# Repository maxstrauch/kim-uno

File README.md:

# KIM Uno

_A portable, software defined dev kit for (retro) microprocessors_

Back in late 2018 it came to my mind, that I wanted to build a small portable microprocessor dev kit, just like the famous [KIM-1](https://en.wikipedia.org/wiki/KIM-1) from MOS Technology, Inc. and designed by Chuck Peddle who was also involved in creating the 6502 CPU.

Therefore, I designed the KIM Uno as a portable device, which fits in one hand and is powered by two CR2032 batteries. It uses the ATMega328p ("Arduino") microcontroller running at 8 MHz to emulate (or simulate) a desired CPU. This architecture also makes sure, that the emulated CPUs are interchangeable to anything which fits inside the microcontroller's flash memory. So it is a multi-purpose device.

Currently this project emulates an [OISC](https://en.wikipedia.org/wiki/One_instruction_set_computer) with just one instruction `subleq`. The idea came to me when I watched [The Ultimate Apollo Guidance Computer Talk](https://www.youtube.com/watch?v=xx7Lfh5SKUQ) and then discovered [this GitHub repo](https://github.com/davidar/subleq).

There is another pretty interesting project, called the same (KIM Uno), which does a real replica of the 6502 KIM Uno. Check it out [here](https://obsolescence.wixsite.com/obsolescence/kim-uno-summary-c1uuh). The creator even sells the kit. So if you are interested in 6502 and like this project, you should take a look there!

# Links

You can find:

 - a very detailed series of build instructions on Instructable: https://www.instructables.com/id/The-KIM-Uno-a-5-Microprocessor-Dev-Kit-Emulator/
 - a video demonstrating the device on YouTube: https://youtu.be/oWd1w513VB8

# Contents of this repository

This repository contains all needed documents, to create your own KIM Uno. In the root of the repository you can find the following important documents:

 - `bom_kim-uno-rev1.ods` - A bill of materials and rough calculation of the material cost (it's about 4,75 € as of 2018) and links to the components on Ebay. The offers on Ebay might be closed (depends on when you read this here) but this might be a good starting point for sourcing the components.
 - `kim-uno-rev1_2018-12-12_gerbers.zip` - A zip file containing the latest Gerber and drill files for production. I send exactly those files out to PCBWay to produce the PCBs. The files are exported to the specifications of PCBWay (see https://www.pcbway.com/blog/help_center/Generate_Gerber_file_from_Kicad.html) but might work also for another manufacturer.
 - `kim-uno-rev1-schematic.pdf` - The schematic of the project. [Show schematics.](https://raw.github.com/maxstrauch/kim-uno/master/kim-uno-rev1-schematic.pdf)
 - `arduino-isp.ino` - An Arduino sketch of the ISP code I use on my Arduino UNO to program the microcontrollers

This are the essential three documents you'll need to reproduce my KIM Uno. Furthermore, the following directories can be found in the repository:

 - `images` - Just images of the project
 - `kicad` - The original KiCad files, so that you can make modifications as you like (see also the License section at the end)
 - `src` - The source code for the microcontroller firmware; you can either use `src/main.hex` and burn it onto your ATMega328p or you can modify `src/main.c`, recompile it (see `src/Makefile`) and then burn it with your own changes
 - `tools` - A little NodeJS based assembler and simulator of the KIM Uno

# Flashing the firmware

In the directory `src/` you can find the source code for the emulator along with an already compiled `src/main.hex` which you can directly upload to the microcontroller.

Before you can actually use it, you need to set the fuse bits of the microcontroller, so that it uses the internal 8 MHz clock without dividing it in half. You can get the job done with the following command:

    avrdude -c stk500v1 -b 9600 -v -v -P /dev/cu.usbmodem1421 -p m328p -U lfuse:w:0xe2:m -U hfuse:w:0xd9:m -U efuse:w:0xff:m

After this you can flash the firmware onto the microcontroller with this command:

    avrdude -c stk500v1 -b 9600 -v -v -P /dev/cu.usbmodem1421 -p m328p -U flash:w:main.hex

Maybe you need to change the argument for `-P`.

You can also use the `src/Makefile` to do this tasks. Run `make all` to compile (GNU AVR toolchain required to be installed) and `make install` to flash it. You can use `make fuse` to set the fuses correctly.

# Theory of operation

## Basics

The KIM Uno does emulate a One Instruction Set Computer (OISC) and provides the subleq instruction to perform computation.

The subleq instruction stands for subtract and branch if less than or equal to zero. In pseudo-code this looks like the following:

    subleq A B C: mem[B] = mem [B] - mem[A]; 
                  if (mem[B] <= 0) goto C;

Since the KIM Uno emulates a 8-bit machine, all arguments A, B and C are 8 bit values and therefore it can address a total main memory of 256 byte. Obviously this can be extended, by making A, B and C multi-byte values. But for now let's keep it simple.

The KIM Uno has also "peripherals": the display and keyboard. It uses a memory mapped architecture to interface those peripherals, although the memory map is very simple:

 - 0x00 = the Z register (zero) and should be kept zero.
 - 0x01 - 0x06 = six bytes which represent the value of every of the display segments (from right to left). A value <= 0xf (16) can be placed in one of this memory locations and it will appear on the seven segment display. There are some special characters to show which can be displayed setting a value > 0xf - see the source code (main.c) for more details.
 - 0x07, 0x08, 0x09 = three bytes where every byte represents two seven segment displays (from right to left). This memory locations allow simply displaying a result without splitting up the result into two nibbles to place it in the single digit memory locations 0x01 - 0x06.
 - 0x0a+ = A program starts at 0x0a. Currently the "Go" key executes from 0x0a fixed.

## Pseudo instructions

There are three "pseudo instructions" which make life easier when programming for the KIM Uno. They are composed of multiple `subleq` instructions:

**MOV a, b - copy data at location a to b can be composed of:**

    subleq b, b, 2 (next instruction)
    subleq a, Z, 3 (next instruction)
    subleq Z, b, 4 (next instruction)
    subleq Z, Z, e.g. 5 (next instruction)

Using the subtraction feature of `subleq`, which `does mem[b] - mem[a]` and overwrites `mem[b]` with the result, the value is copied using the zero register. And `subleq Z, Z, ...` simply resets the zero register to 0, regardless of the value of Z.

**ADD a, b - adds the values a + b and stores the sum in b can be composed of:**

    subleq a, Z, 2 (next instruction)
    subleq Z, b, 3 (next instruction)
    subleq Z, Z, e.g. 4 (next instruction)

This instruction simply calculates `mem[b] - (- mem[a])` which is `mem[b] + mem[a]` by also using the subtraction feature.

**HLT - halts the CPU and ends the execution:**

By definition the emulator knows that the CPU wants to terminate if it jumps to 0xff (or -1 if singed). So a simple

    subleq Z, Z, -1

does the job and indicates to the emulator, that it should end emulation.

## Fibonacci example program

With this information one can now write a program in assembler, for example Fibonacci's algorithm:

    .def n   0xfa 6             ; Input n for fibonacci
    .def a   0xfc 0
    .def b   0xfd 1
    .def out 0x07 0             ; Output register for display

    ; Temp registeres, needed since the subleq instructions modify the original
    ; registers (the program might be optimized to use only one tmp register)
    .def tmp1 0xfe 0
    .def tmp2 0xff 0

    ; Constant values. Since subleq has no immediate instructions we store
    ; those values in a register
    .def Z   0x00 0
    .def one 0xfb 1
    .def two 0xf9 2

        mov n, tmp1             ; Copy n to tmp1 to perform calculation on it
        subleq two, tmp1, done  ; If n <= 2, we're done and goto the end
        subleq one, n, loop     ; Start computation with n := n-1

    loop:
        mov a, tmp1             ; Save a and ...
        mov b, tmp2             ; ... b to perform the addition on it
        add tmp1, tmp2          ; Save the sum of a and b on tmp2
        mov b, a                ; Set a to the value of b
        mov tmp2, b             ; Set b to tmp2 which is a + b
        subleq one, n, done     ; Decrement n
        subleq Z, Z, loop       ; Check if n > 0 and continue computation

    done:
        mov b, out              ; Finished ;-) - output the value on b
        hlt                     ; Halt the CPU

This is basically the content of `tools/fibonacci/fibonacci.s`. This program can now be turned into `subleq` CPU instructions and entered into the memory of the KIM Uno and then executed. Since there is only one instruction, only the arguments (A, B and C) are entered. So after three memory locations the next instruction arguments begin and so forth.

But there is a faster way, shown in the next section.

## Further tools

The `tools/` directory contains some basic assembler and simulator for the KIM Uno. They are written in [NodeJS](https://nodejs.org/en/) - make sure that you have installed it.

**Assembling programs**

If you take a look at "tools/fibonacci/fibonacci.s" you'll find that it is the source code for the discussed fibonacci implementation. To assemble it and make a program out of it, that the KIM Uno can run, you enter the following command (in `tools/`):

    node assemble.js fibonacci/fibonacci.s

and it will either print an error if you made a mistake or spill out the resulting program. To save it, you can copy the output and save it to a file or simply run this command:

    node assemble.js fibonacci/fibonacci.s > yourfile.h

The output is formatted in a way that it can be directly included in the KIM Uno firmware as a C header file, but the simulator can also use it to simulate. Simply enter:

    node sim.js yourfile.h

And you will be presented with the simulation result and the output expected from the KIM Uno on the display.

# Conclusion

## Design flaws in the PCB design

After completing this project I found a couple of points which are noteworthy and should be addressed in a new revision of the PCB board:

- the ATMega328p's silk screen has not the usual notch where the first pin is located. The DIP-28 footprint does not even have a square pad where the first pin is located. This should definitely be improved with a more detailed silkscreen to prevent confusion
- the ISP header has no connection labels on the silk screen. This makes it difficult to recognize how to connect it to the ISP
- the ISP header could be changed into a 2x6 pin header with a standard pin layout to prevent any confusion

Apart from those points I'm pretty happy how it turned out and worked on the first try.

## Further uses

But the journey does not end here - there are an infinite number of options how you could modify the KIM Uno and customize it to your needs and liking.

For example the KIM Uno could be equipped with a "real" retro CPU emulator which might emulate the famous MOS 6502 or Intel 8085, 8086 or 8088. Then it would go the way to my initial vision, before I learned about OISCs.

But there are possible other uses, since the hardware design is pretty generic. The KIM Uno could be used as:

- a remote controller e.g. for CNCs or other devices. Maybe wired or equipped with an IR diode or any other wireless sender
- a (hexadecimal) pocket calculator. The firmware can be adapted very easily and the board design does not need to be changed very much. Maybe the silkscreen can be adapted with math operations and the gap between the segments can be removed. Apart from this, it is already ready for this transformation

_**Have fun with it. Cheers!**_

# License

Creative Commons Attribution-ShareAlike 4.0 International (CC BY-SA 4.0). Click [here](http://creativecommons.org/licenses/by-sa/4.0/) for details. The license applies to the entire source code.

`This program is distributed WITHOUT ANY WARRANTY; without even the implied warranty of MERCHANTABILITY or FITNESS FOR A PARTICULAR PURPOSE.`

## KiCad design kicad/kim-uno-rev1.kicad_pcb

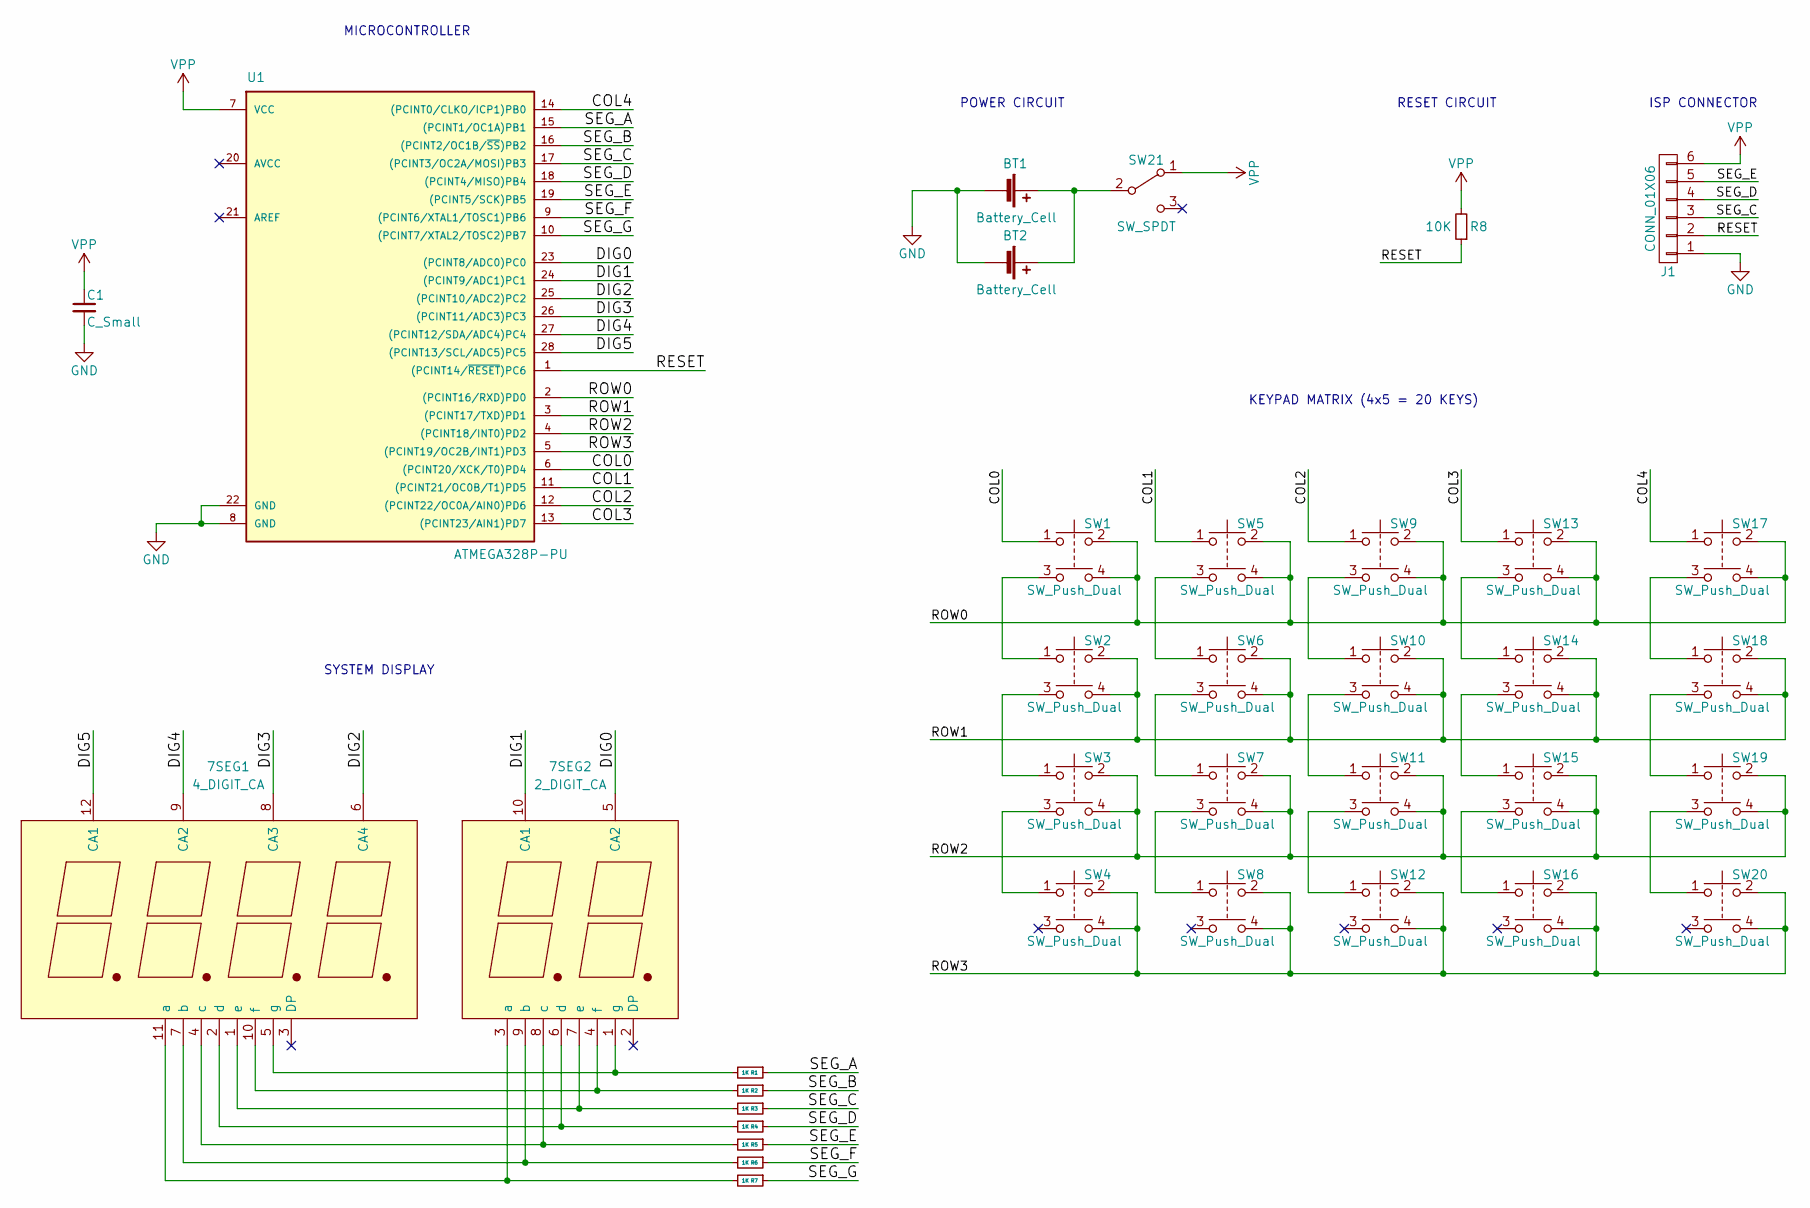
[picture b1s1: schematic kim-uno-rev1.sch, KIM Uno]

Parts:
7SEG1: 4_DIGIT_CA; 7_Segment_4_Digit
7SEG2: 2_DIGIT_CA; 7_Segment_2_Digit
BT1, BT2: Battery_Cell; CR2032SMD
C1: C_Small; C_Disc_D5.0mm_W2.5mm_P2.50mm
J1: CONN_01X06; Pin_Header_Straight_1x06_Pitch2.54mm
R1, R2, R3, R4, R5, R6, R7: 1K; R_Axial_DIN0204_L3.6mm_D1.6mm_P7.62mm_Horizontal
R8: 10K; R_Axial_DIN0204_L3.6mm_D1.6mm_P7.62mm_Horizontal
SW1, SW2, SW3, SW4, SW5, SW6, SW7, SW8, SW9, SW10, SW11, SW12, SW13, SW14, SW15, SW16, SW17, SW18, SW19, SW20: SW_Push_Dual; SMD_Tact_Switch_6x6x6_Big_Pads
SW21: SW_SPDT; Switch_SPDT_3mm
U1: ATMEGA328P-PU; DIP-28_W7.62mm

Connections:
/COL0: SW1.1, U1.6 ((PCINT20/XCK/T0)PD4)
/COL1: SW5.1, U1.11 ((PCINT21/OC0B/T1)PD5)
/COL2: SW9.1, U1.12 ((PCINT22/OC0A/AIN0)PD6)
/COL3: SW13.1, U1.13 ((PCINT23/AIN1)PD7)
/COL4: SW17.1, U1.14 ((PCINT0/CLKO/ICP1)PB0)
/DIG0: 7SEG2.5 (CA2), U1.23 ((PCINT8/ADC0)PC0)
/DIG1: 7SEG2.10 (CA1), U1.24 ((PCINT9/ADC1)PC1)
/DIG2: 7SEG1.6 (CA4), U1.25 ((PCINT10/ADC2)PC2)
/DIG3: 7SEG1.8 (CA3), U1.26 ((PCINT11/ADC3)PC3)
/DIG4: 7SEG1.9 (CA2), U1.27 ((PCINT12/SDA/ADC4)PC4)
/DIG5: 7SEG1.12 (CA1), U1.28 ((PCINT13/SCL/ADC5)PC5)
/RESET: J1.2, R8.1, U1.1 ((PCINT14/~RESET~)PC6)
/ROW0: SW1.2, SW1.4, SW5.2, SW5.4, SW9.2, SW9.4, SW13.2, SW13.4, SW17.2, SW17.4, U1.2 ((PCINT16/RXD)PD0)
/ROW1: SW2.2, SW2.4, SW6.2, SW6.4, SW10.2, SW10.4, SW14.2, SW14.4, SW18.2, SW18.4, U1.3 ((PCINT17/TXD)PD1)
/ROW2: SW3.2, SW3.4, SW7.2, SW7.4, SW11.2, SW11.4, SW15.2, SW15.4, SW19.2, SW19.4, U1.4 ((PCINT18/INT0)PD2)
/ROW3: SW4.2, SW4.4, SW8.2, SW8.4, SW12.2, SW12.4, SW16.2, SW16.4, SW20.2, SW20.4, U1.5 ((PCINT19/OC2B/INT1)PD3)
/SEG_A: R1.1, U1.15 ((PCINT1/OC1A)PB1)
/SEG_B: R2.1, U1.16 ((PCINT2/OC1B/~SS~)PB2)
/SEG_C: J1.3, R3.1, U1.17 ((PCINT3/OC2A/MOSI)PB3)
/SEG_D: J1.4, R4.1, U1.18 ((PCINT4/MISO)PB4)
/SEG_E: J1.5, R5.1, U1.19 ((PCINT5/SCK)PB5)
/SEG_F: R6.1, U1.9 ((PCINT6/XTAL1/TOSC1)PB6)
/SEG_G: R7.1, U1.10 ((PCINT7/XTAL2/TOSC2)PB7)
GND: BT1.2 (-), BT2.2 (-), C1.2, J1.1, U1.8 (GND), U1.22 (GND)
unnamed: 7SEG1.1 (e), 7SEG2.7 (e), R3.2
unnamed: 7SEG1.2 (d), 7SEG2.6 (d), R4.2
unnamed: 7SEG1.4 (c), 7SEG2.8 (c), R5.2
unnamed: 7SEG1.5 (g), 7SEG2.1 (g), R1.2
unnamed: 7SEG1.7 (b), 7SEG2.9 (b), R6.2
unnamed: 7SEG1.10 (f), 7SEG2.4 (f), R2.2
unnamed: 7SEG1.11 (a), 7SEG2.3 (a), R7.2
unnamed: BT1.1 (+), BT2.1 (+), SW21.2 (B)
unnamed: SW1.3, SW2.1
unnamed: SW2.3, SW3.1
unnamed: SW3.3, SW4.1
unnamed: SW5.3, SW6.1
unnamed: SW6.3, SW7.1
unnamed: SW7.3, SW8.1
unnamed: SW9.3, SW10.1
unnamed: SW10.3, SW11.1
unnamed: SW11.3, SW12.1
unnamed: SW13.3, SW14.1
unnamed: SW14.3, SW15.1
unnamed: SW15.3, SW16.1
unnamed: SW17.3, SW18.1
unnamed: SW18.3, SW19.1
unnamed: SW19.3, SW20.1
VPP: C1.1, J1.6, R8.2, SW21.1 (A), U1.7 (VCC)

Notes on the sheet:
POWER CIRCUIT
RESET CIRCUIT
ISP CONNECTOR
MICROCONTROLLER
SYSTEM DISPLAY
KEYPAD MATRIX (4x5 = 20 KEYS)

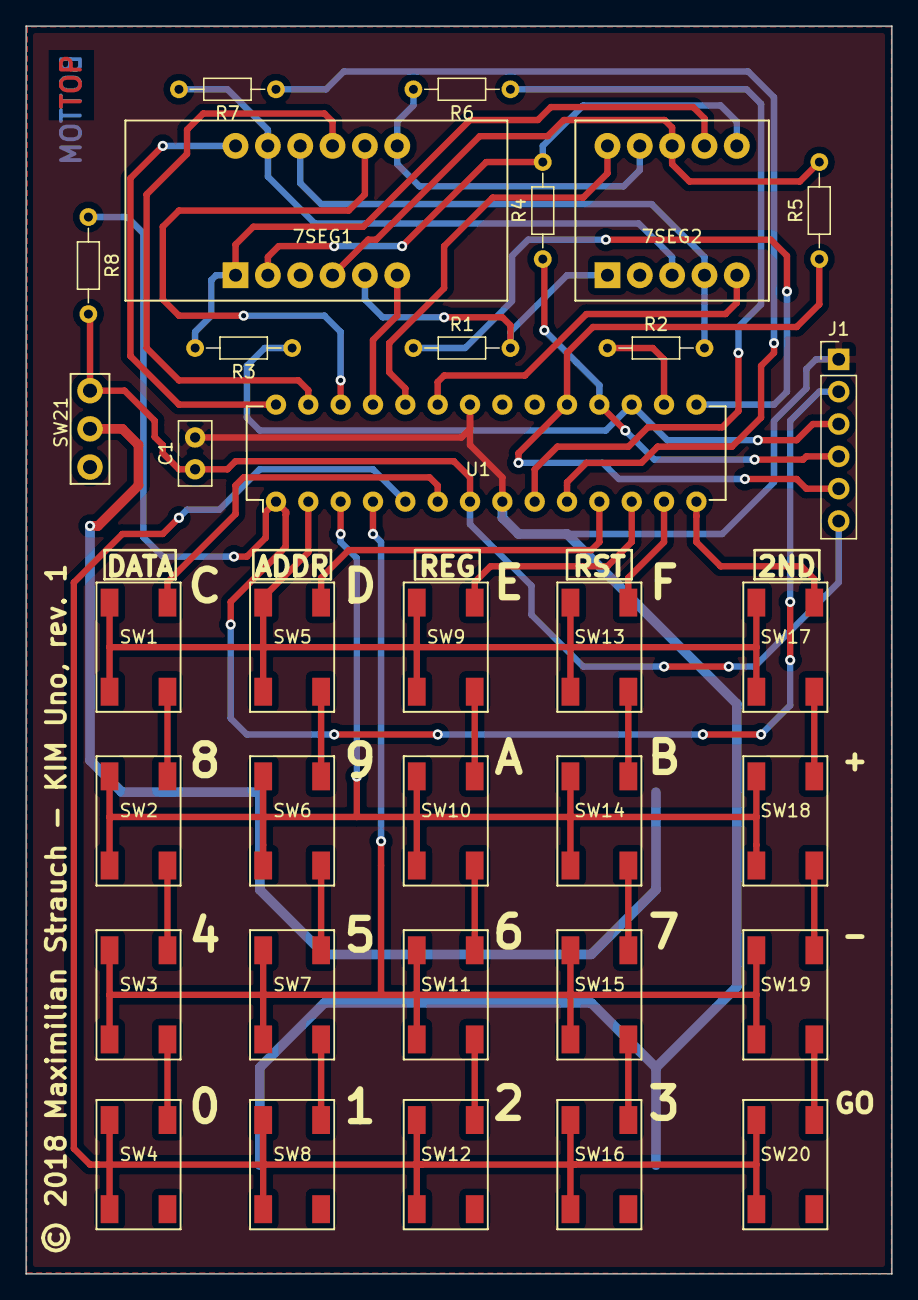
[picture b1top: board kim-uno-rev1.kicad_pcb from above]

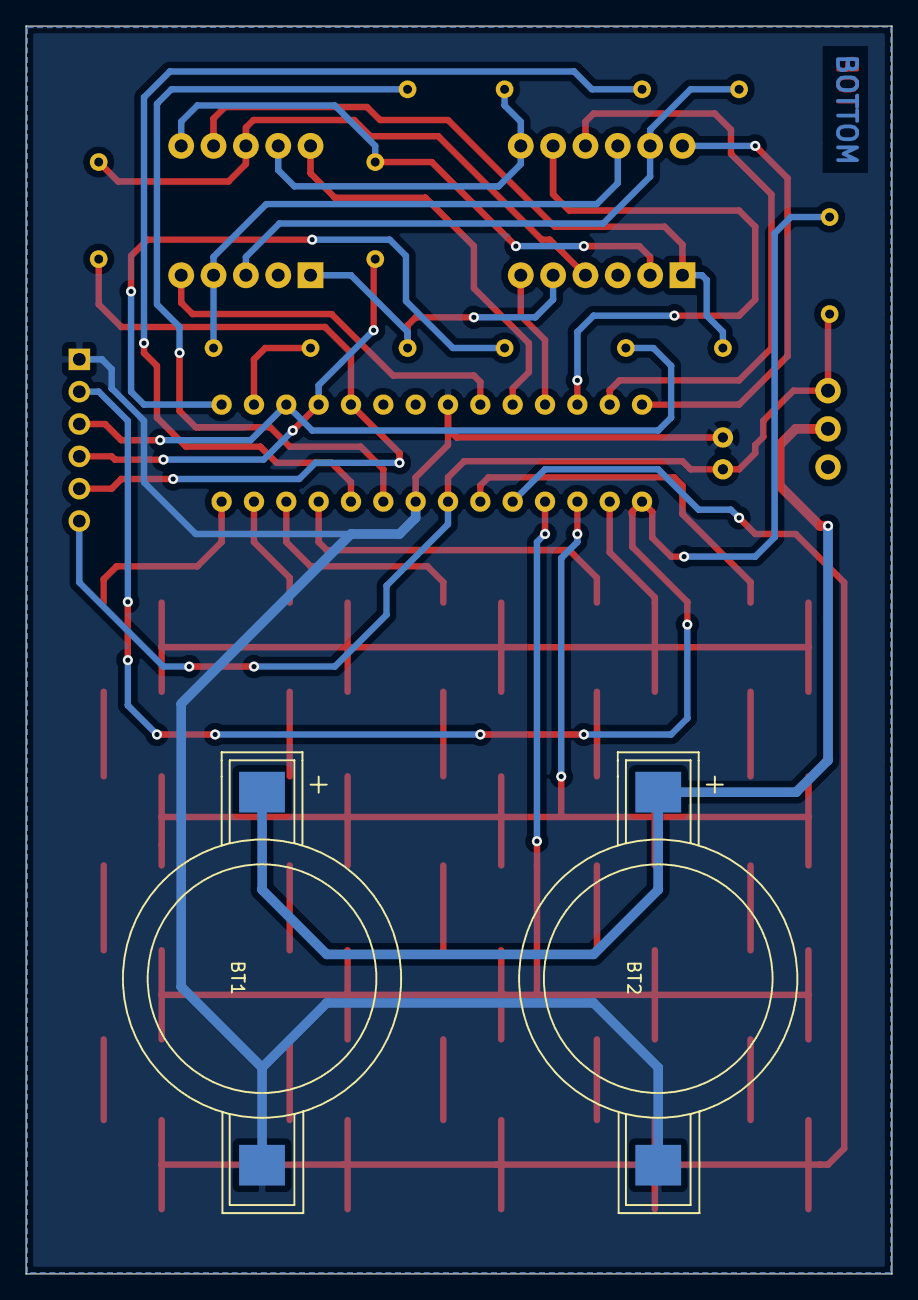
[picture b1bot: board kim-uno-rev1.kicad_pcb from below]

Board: 2 copper layers, 68.0 x 98.0 mm, 36 parts (2 on the bottom side), 48 nets.

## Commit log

2019-05-26 Added reference to similar project

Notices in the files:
kicad/kim-uno-rev1.kicad_pcb:
© 2018 Maximilian Strauch - KIM Uno, rev. 1
